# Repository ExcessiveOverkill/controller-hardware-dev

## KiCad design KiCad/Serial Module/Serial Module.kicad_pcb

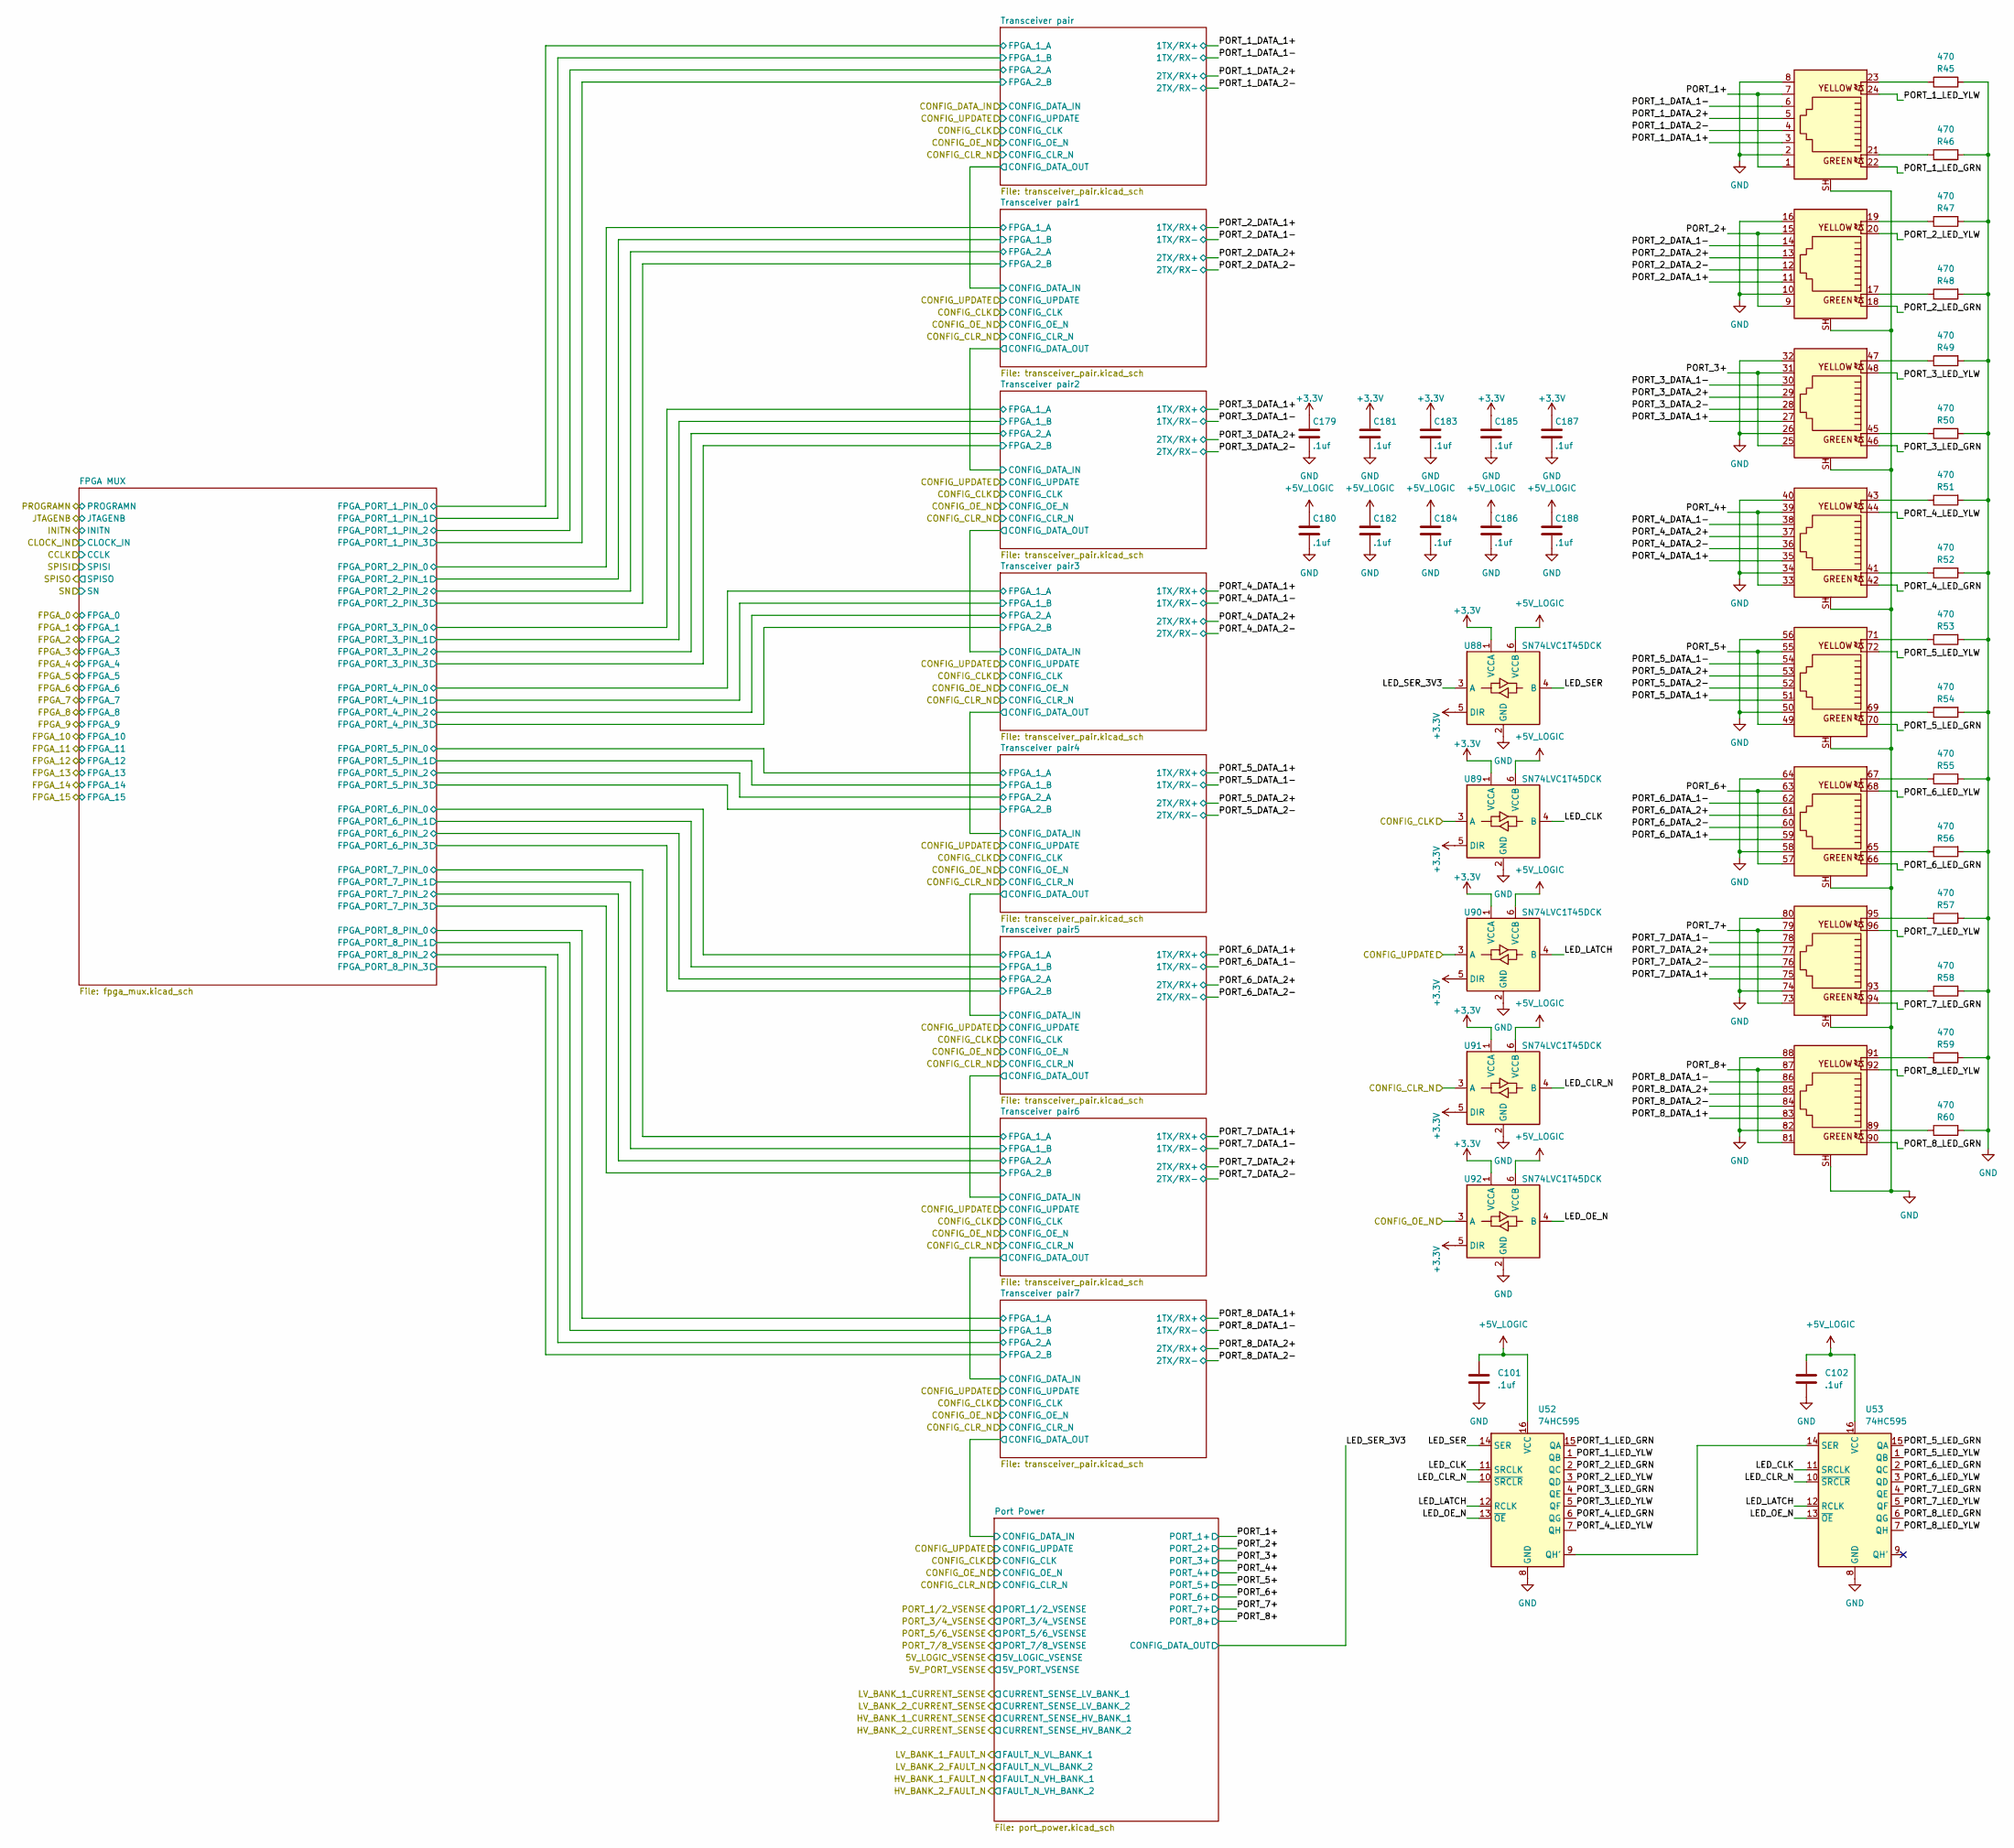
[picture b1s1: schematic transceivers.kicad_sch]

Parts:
C101, C102, C179, C180, C181, C182, C183, C184, C185, C186, C187, C188: .1uf; C_0402_1005Metric; Part number CC0402KRX7R9BB104; LCSC# C131394
J3: RJ45-TH_HC-RJ45-059D-2X4-2-04; Part number HC-RJ45-059D-2*4-2-04; LCSC# C46261621
R45, R46, R47, R48, R49, R50, R51, R52, R53, R54, R55, R56, R57, R58, R59, R60: 470; R_0402_1005Metric; Part number RC0402FR-07470RL; LCSC# C114877
U52, U53: 74HC595; DHVQFN-16-1EP_2.5x3.5mm_P0.5mm_EP1x2mm; Part number 74HC595BQ,115; LCSC# C730243
U88, U89, U90, U91, U92: SN74LVC1T45DCK; SOT-363_SC-70-6; Part number SN74LVC1T45DCKR; LCSC# C9382

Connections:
+3.3V: C179.1, C181.1, C183.1, C185.1, C187.1, U88.1 (VCCA), U88.5 (DIR), U89.1 (VCCA), U89.5 (DIR), U90.1 (VCCA), U90.5 (DIR), U91.1 (VCCA), U91.5 (DIR), U92.1 (VCCA), U92.5 (DIR); also elsewhere on the board
+5V_LOGIC: C101.1, C102.1, C180.1, C182.1, C184.1, C186.1, C188.1, U52.16 (VCC), U53.16 (VCC), U88.6 (VCCB), U89.6 (VCCB), U90.6 (VCCB), U91.6 (VCCB), U92.6 (VCCB); also elsewhere on the board
/MCU/CONFIG_CLK: U89.3 (A); also elsewhere on the board
/MCU/CONFIG_CLR_N: U91.3 (A); also elsewhere on the board
/MCU/CONFIG_OE_N: U92.3 (A); also elsewhere on the board
/MCU/CONFIG_UPDATE: U90.3 (A); also elsewhere on the board
/Transceivers/LED_CLK: U52.11 (SRCLK), U53.11 (SRCLK), U89.4 (B)
/Transceivers/LED_CLR_N: U52.10 (~SRCLR), U53.10 (~SRCLR), U91.4 (B)
/Transceivers/LED_LATCH: U52.12 (RCLK), U53.12 (RCLK), U90.4 (B)
/Transceivers/LED_OE_N: U52.13 (~OE), U53.13 (~OE), U92.4 (B)
/Transceivers/LED_SER: U52.14 (SER), U88.4 (B)
/Transceivers/LED_SER_3V3: U88.3 (A); also elsewhere on the board
/Transceivers/PORT_1+: J3.1, J3.7; also elsewhere on the board
/Transceivers/PORT_1_DATA_1+: J3.3; also elsewhere on the board
/Transceivers/PORT_1_DATA_1-: J3.6; also elsewhere on the board
/Transceivers/PORT_1_DATA_2+: J3.5; also elsewhere on the board
/Transceivers/PORT_1_DATA_2-: J3.4; also elsewhere on the board
/Transceivers/PORT_1_LED_GRN: J3.22, U52.15 (QA)
/Transceivers/PORT_1_LED_YLW: J3.24, U52.1 (QB)
/Transceivers/PORT_2+: J3.9, J3.15; also elsewhere on the board
/Transceivers/PORT_2_DATA_1+: J3.11; also elsewhere on the board
/Transceivers/PORT_2_DATA_1-: J3.14; also elsewhere on the board
/Transceivers/PORT_2_DATA_2+: J3.13; also elsewhere on the board
/Transceivers/PORT_2_DATA_2-: J3.12; also elsewhere on the board
/Transceivers/PORT_2_LED_GRN: J3.18, U52.2 (QC)
/Transceivers/PORT_2_LED_YLW: J3.20, U52.3 (QD)
/Transceivers/PORT_3+: J3.25, J3.31; also elsewhere on the board
/Transceivers/PORT_3_DATA_1+: J3.27; also elsewhere on the board
/Transceivers/PORT_3_DATA_1-: J3.30; also elsewhere on the board
/Transceivers/PORT_3_DATA_2+: J3.29; also elsewhere on the board
/Transceivers/PORT_3_DATA_2-: J3.28; also elsewhere on the board
/Transceivers/PORT_3_LED_GRN: J3.46, U52.4 (QE)
/Transceivers/PORT_3_LED_YLW: J3.48, U52.5 (QF)
/Transceivers/PORT_4+: J3.33, J3.39; also elsewhere on the board
/Transceivers/PORT_4_DATA_1+: J3.35; also elsewhere on the board
/Transceivers/PORT_4_DATA_1-: J3.38; also elsewhere on the board
/Transceivers/PORT_4_DATA_2+: J3.37; also elsewhere on the board
/Transceivers/PORT_4_DATA_2-: J3.36; also elsewhere on the board
/Transceivers/PORT_4_LED_GRN: J3.42, U52.6 (QG)
/Transceivers/PORT_4_LED_YLW: J3.44, U52.7 (QH)
/Transceivers/PORT_5+: J3.49, J3.55; also elsewhere on the board
/Transceivers/PORT_5_DATA_1+: J3.51; also elsewhere on the board
/Transceivers/PORT_5_DATA_1-: J3.54; also elsewhere on the board
/Transceivers/PORT_5_DATA_2+: J3.53; also elsewhere on the board
/Transceivers/PORT_5_DATA_2-: J3.52; also elsewhere on the board
/Transceivers/PORT_5_LED_GRN: J3.70, U53.15 (QA)
/Transceivers/PORT_5_LED_YLW: J3.72, U53.1 (QB)
/Transceivers/PORT_6+: J3.57, J3.63; also elsewhere on the board
/Transceivers/PORT_6_DATA_1+: J3.59; also elsewhere on the board
/Transceivers/PORT_6_DATA_1-: J3.62; also elsewhere on the board
/Transceivers/PORT_6_DATA_2+: J3.61; also elsewhere on the board
/Transceivers/PORT_6_DATA_2-: J3.60; also elsewhere on the board
/Transceivers/PORT_6_LED_GRN: J3.66, U53.2 (QC)
/Transceivers/PORT_6_LED_YLW: J3.68, U53.3 (QD)
/Transceivers/PORT_7+: J3.73, J3.79; also elsewhere on the board
/Transceivers/PORT_7_DATA_1+: J3.75; also elsewhere on the board
/Transceivers/PORT_7_DATA_1-: J3.78; also elsewhere on the board
/Transceivers/PORT_7_DATA_2+: J3.77; also elsewhere on the board
/Transceivers/PORT_7_DATA_2-: J3.76; also elsewhere on the board
/Transceivers/PORT_7_LED_GRN: J3.94, U53.4 (QE)
/Transceivers/PORT_7_LED_YLW: J3.96, U53.5 (QF)
/Transceivers/PORT_8+: J3.81, J3.87; also elsewhere on the board
/Transceivers/PORT_8_DATA_1+: J3.83; also elsewhere on the board
/Transceivers/PORT_8_DATA_1-: J3.86; also elsewhere on the board
/Transceivers/PORT_8_DATA_2+: J3.85; also elsewhere on the board
/Transceivers/PORT_8_DATA_2-: J3.84; also elsewhere on the board
/Transceivers/PORT_8_LED_GRN: J3.90, U53.6 (QG)
/Transceivers/PORT_8_LED_YLW: J3.92, U53.7 (QH)
GND: C101.2, C102.2, C179.2, C180.2, C181.2, C182.2, C183.2, C184.2, C185.2, C186.2, C187.2, C188.2, J3.2, J3.8, J3.10, J3.16, J3.26, J3.32, J3.34, J3.40, J3.50, J3.56, J3.58, J3.64, J3.74, J3.80, J3.82, J3.88, J3.SH, R45.2, R46.2, R47.2, R48.2, R49.2, R50.2, R51.2, R52.2, R53.2, R54.2, R55.2, R56.2, R57.2, R58.2, R59.2, R60.2, U52.8 (GND), U53.8 (GND), U88.2 (GND), U89.2 (GND), U90.2 (GND), U91.2 (GND), U92.2 (GND); also elsewhere on the board
unnamed: J3.17, R48.1
unnamed: J3.19, R47.1
unnamed: J3.21, R46.1
unnamed: J3.23, R45.1
unnamed: J3.41, R52.1
unnamed: J3.43, R51.1
unnamed: J3.45, R50.1
unnamed: J3.47, R49.1
unnamed: J3.65, R56.1
unnamed: J3.67, R55.1
unnamed: J3.69, R54.1
unnamed: J3.71, R53.1
unnamed: J3.89, R60.1
unnamed: J3.91, R59.1
unnamed: J3.93, R58.1
unnamed: J3.95, R57.1
unnamed: U52.9 (QH'), U53.14 (SER)

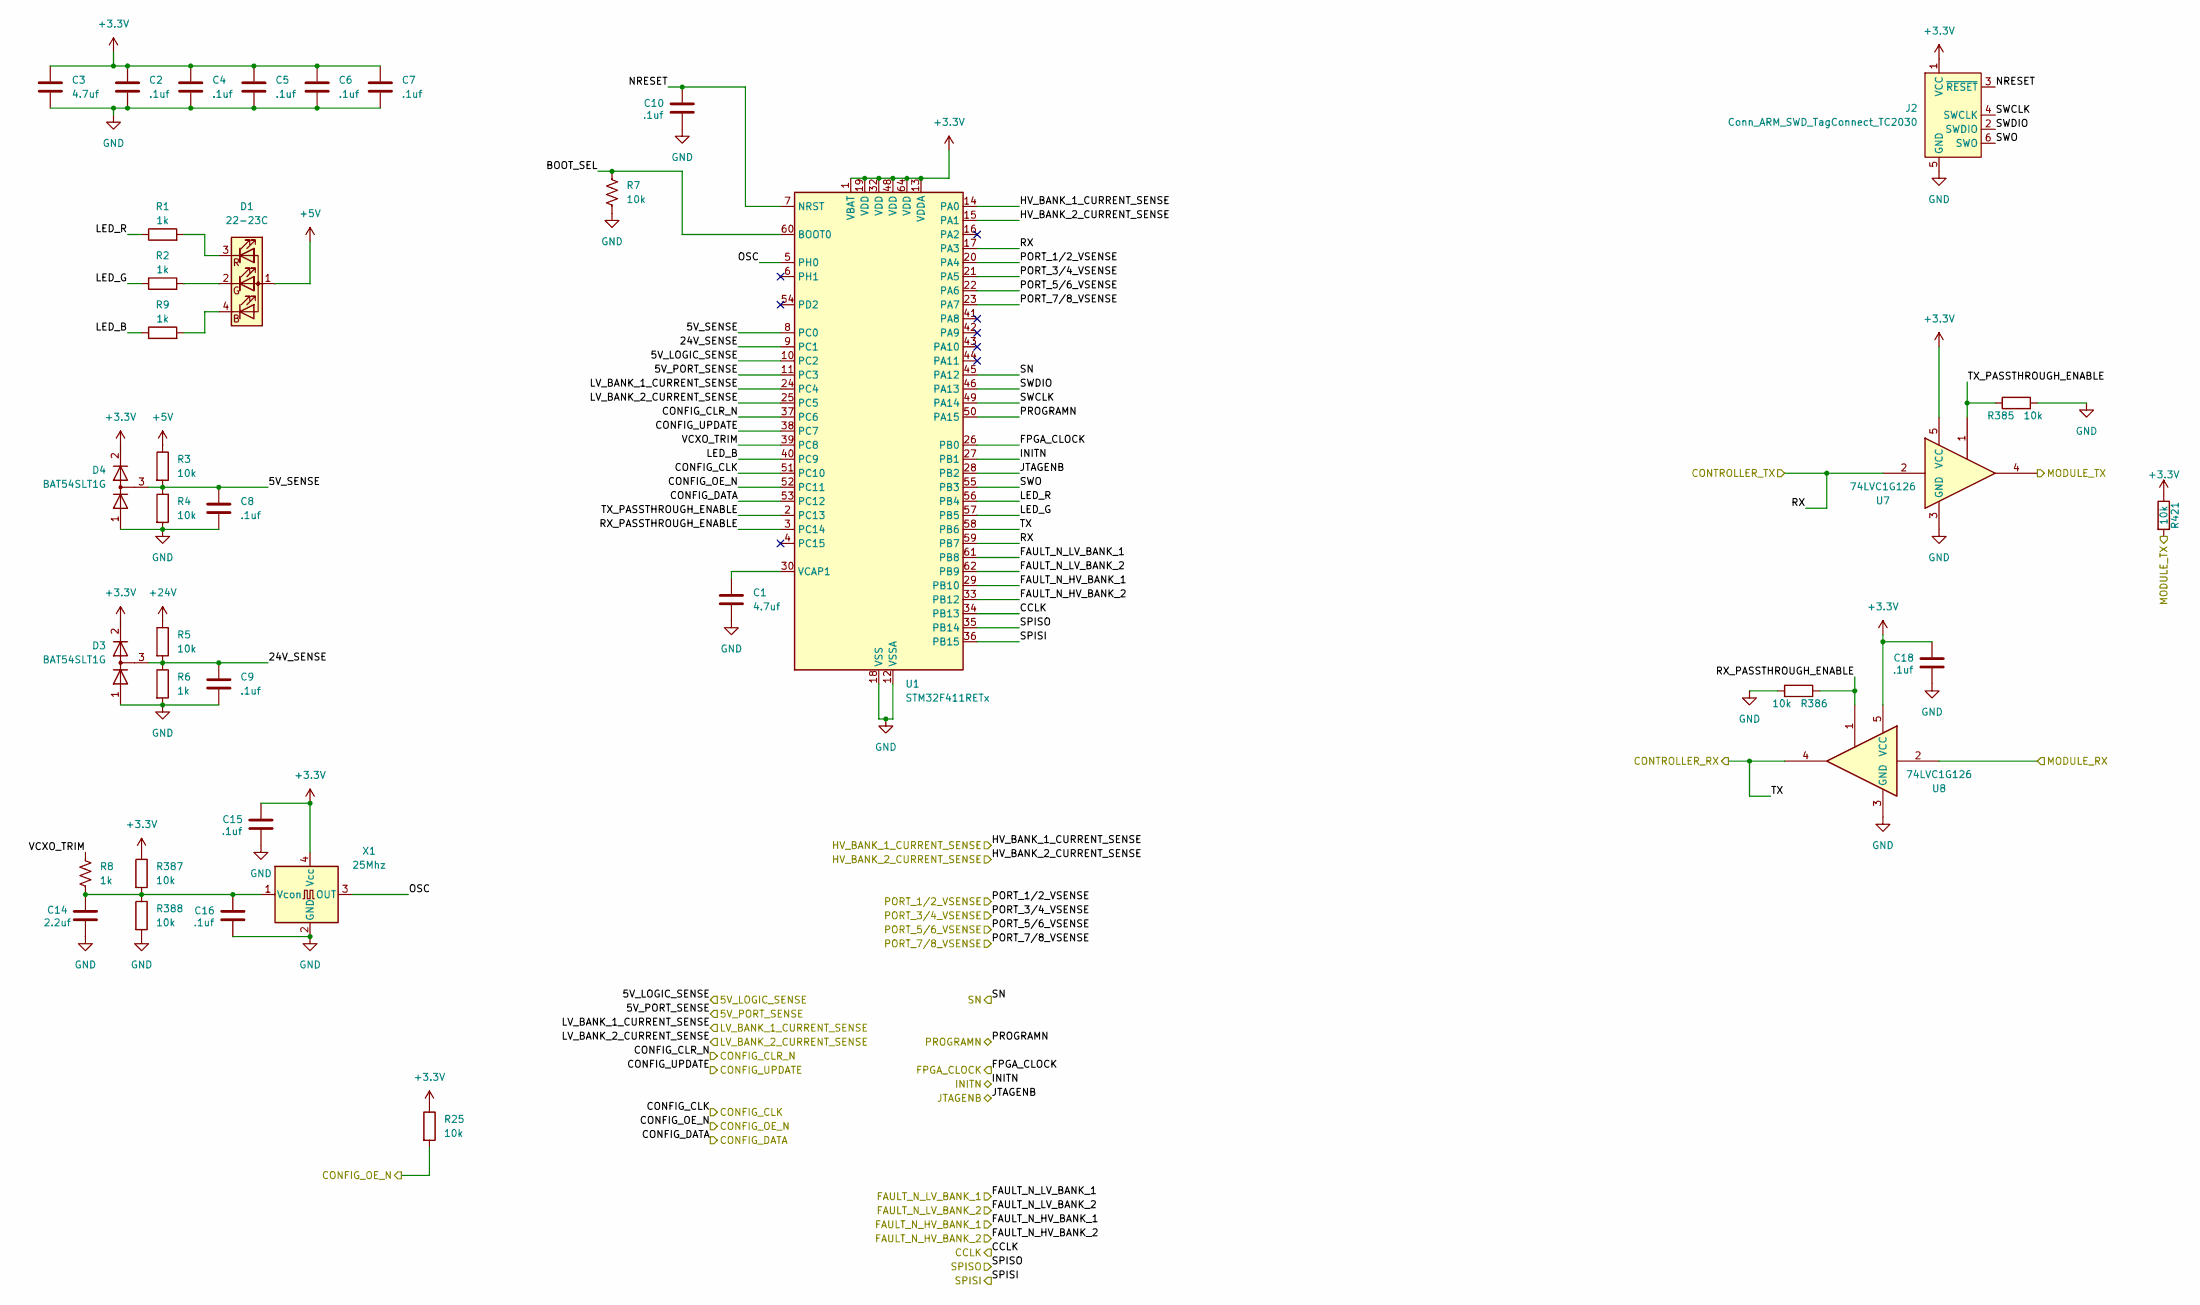
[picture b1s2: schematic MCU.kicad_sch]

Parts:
C1: 4.7uf; C_0402_1005Metric; Part number CC0402MRX5R6BB475; LCSC# C469468
C2, C4, C5, C6, C7, C8, C9, C10, C15, C16, C18: .1uf; C_0402_1005Metric; Part number CC0402KRX7R9BB104; LCSC# C131394
C3: 4.7uf; C_0603_1608Metric; Part number CC0603KRX5R7BB475; LCSC# C277476
C14: 2.2uf; C_0402_1005Metric; Part number CC0402KRX5R6BB225; LCSC# C326606
D1: 22-23C; 22-23C_EVE; Part number 22-23C/R6GHBHW-C01/2C; LCSC# C181865
D3, D4: BAT54SLT1G; SOT-23; Part number LBAT54SLT1G; LCSC# C12765
J2: Conn_ARM_SWD_TagConnect_TC2030; Tag-Connect_TC2030-IDC-FP_2x03_P1.27mm_Vertical; Part number N/A - Tag-Connect TC2030 pads only (no 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
R1, R2, R6, R8, R9: 1k; R_0402_1005Metric; Part number RC0402FR-071KL; LCSC# C106235
R3, R4, R5, R7, R25, R385, R386, R387, R388, R421: 10k; R_0402_1005Metric; Part number RC0402FR-0710KL; LCSC# C60490
U1: STM32F411RETx; LQFP-64_10x10mm_P0.5mm; Part number STM32F411RET6; LCSC# C94355
U7, U8: 74LVC1G126; SOT-353_SC-70-5; Part number 74LVC1G126CT05ARCQ; LCSC# C48391411
X1: 25Mhz; Oscillator_SMD_Abracon_ASE-4Pin_3.2x2.5mm; Part number SX3V25.000B20100F30TNN; LCSC# C5179998

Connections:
+3.3V: C2.1, C3.1, C4.1, C5.1, C6.1, C7.1, C15.2, C18.2, D3.2 (K), D4.2 (K), J2.1 (VCC), R25.1, R387.1, R421.1, U1.1 (VBAT), U1.13 (VDDA), U1.19 (VDD), U1.32 (VDD), U1.48 (VDD), U1.64 (VDD), U7.5 (VCC), U8.5 (VCC), X1.4 (Vcc); also elsewhere on the board
+5V: D1.1 (A), R3.1; also elsewhere on the board
+24V: R5.1; also elsewhere on the board
/FPGA Connector/MODULE_RX: U8.2; also elsewhere on the board
/FPGA Connector/MODULE_TX: R421.2, U7.4; also elsewhere on the board
/MCU/5V_LOGIC_SENSE: U1.10 (PC2); also elsewhere on the board
/MCU/5V_PORT_SENSE: U1.11 (PC3); also elsewhere on the board
/MCU/5V_SENSE: C8.1, D4.3 (common), R3.2, R4.1, U1.8 (PC0)
/MCU/24V_SENSE: C9.1, D3.3 (common), R5.2, R6.1, U1.9 (PC1)
/MCU/BOOT_SEL: R7.2, U1.60 (BOOT0)
/MCU/CCLK: U1.34 (PB13); also elsewhere on the board
/MCU/CONFIG_CLK: U1.51 (PC10); also elsewhere on the board
/MCU/CONFIG_CLR_N: U1.37 (PC6); also elsewhere on the board
/MCU/CONFIG_DATA: U1.53 (PC12); also elsewhere on the board
/MCU/CONFIG_OE_N: R25.2, U1.52 (PC11); also elsewhere on the board
/MCU/CONFIG_UPDATE: U1.38 (PC7); also elsewhere on the board
/MCU/FAULT_N_HV_BANK_1: U1.29 (PB10); also elsewhere on the board
/MCU/FAULT_N_HV_BANK_2: U1.33 (PB12); also elsewhere on the board
/MCU/FAULT_N_LV_BANK_1: U1.61 (PB8); also elsewhere on the board
/MCU/FAULT_N_LV_BANK_2: U1.62 (PB9); also elsewhere on the board
/MCU/FPGA_CLOCK: U1.26 (PB0); also elsewhere on the board
/MCU/HV_BANK_1_CURRENT_SENSE: U1.14 (PA0); also elsewhere on the board
/MCU/HV_BANK_2_CURRENT_SENSE: U1.15 (PA1); also elsewhere on the board
/MCU/INITN: U1.27 (PB1); also elsewhere on the board
/MCU/JTAGENB: U1.28 (PB2); also elsewhere on the board
/MCU/LED_B: R9.1, U1.40 (PC9)
/MCU/LED_G: R2.1, U1.57 (PB5)
/MCU/LED_R: R1.1, U1.56 (PB4)
/MCU/LV_BANK_1_CURRENT_SENSE: U1.24 (PC4); also elsewhere on the board
/MCU/LV_BANK_2_CURRENT_SENSE: U1.25 (PC5); also elsewhere on the board
/MCU/NRESET: C10.2, J2.3 (~RESET), U1.7 (NRST)
/MCU/OSC: U1.5 (PH0), X1.3 (OUT)
/MCU/PORT_1/2_VSENSE: U1.20 (PA4); also elsewhere on the board
/MCU/PORT_3/4_VSENSE: U1.21 (PA5); also elsewhere on the board
/MCU/PORT_5/6_VSENSE: U1.22 (PA6); also elsewhere on the board
/MCU/PORT_7/8_VSENSE: U1.23 (PA7); also elsewhere on the board
/MCU/PROGRAMN: U1.50 (PA15); also elsewhere on the board
/MCU/RX: U1.17 (PA3), U1.59 (PB7), U7.2; also elsewhere on the board
/MCU/RX_PASSTHROUGH_ENABLE: R386.1, U1.3 (PC14), U8.1
/MCU/SN: U1.45 (PA12); also elsewhere on the board
/MCU/SPISI: U1.36 (PB15); also elsewhere on the board
/MCU/SPISO: U1.35 (PB14); also elsewhere on the board
/MCU/SWCLK: J2.4 (SWCLK), U1.49 (PA14)
/MCU/SWDIO: J2.2 (SWDIO), U1.46 (PA13)
/MCU/SWO: J2.6 (SWO), U1.55 (PB3)
/MCU/TX: U1.58 (PB6), U8.4; also elsewhere on the board
/MCU/TX_PASSTHROUGH_ENABLE: R385.1, U1.2 (PC13), U7.1
/MCU/VCXO_TRIM: R8.1, U1.39 (PC8)
GND: C1.2, C2.2, C3.2, C4.2, C5.2, C6.2, C7.2, C8.2, C9.2, C10.1, C14.1, C15.1, C16.1, C18.1, D3.1 (A), D4.1 (A), J2.5 (GND), R4.2, R6.2, R7.1, R385.2, R386.2, R388.2, U1.12 (VSSA), U1.18 (VSS), U1.31 (VSS), U1.47 (VSS), U1.63 (VSS), U7.3 (GND), U8.3 (GND), X1.2 (GND); also elsewhere on the board
unnamed: D1.4 (BK), R9.2
unnamed: D1.2 (GK), R2.2
unnamed: D1.3 (RK), R1.2
unnamed: C1.1, U1.30 (VCAP1)
unnamed: C14.2, C16.2, R8.2, R387.2, R388.1, X1.1 (Vcon)

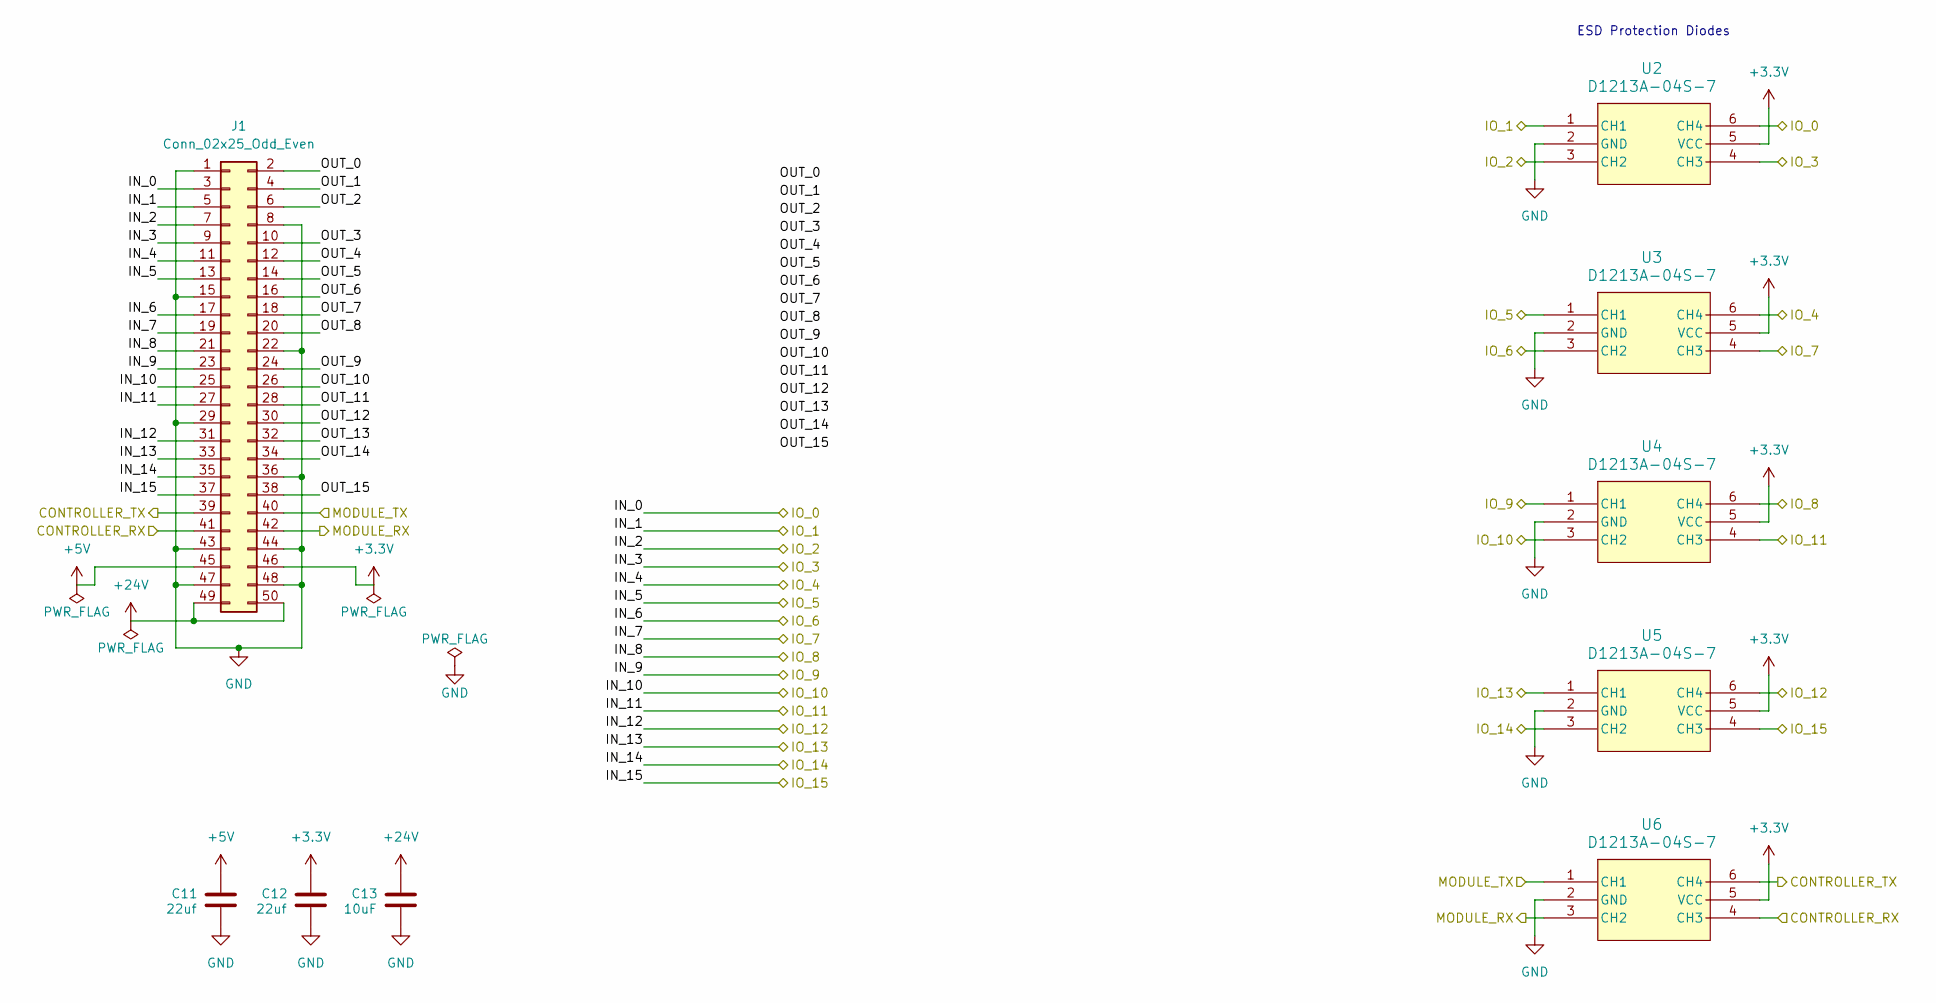
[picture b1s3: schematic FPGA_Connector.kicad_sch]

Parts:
C11, C12: 22uf; C_0805_2012Metric; Part number CC0805MKX5R8BB226; LCSC# C784585
C13: 10uF; C_1210_3225Metric; Part number CC1210KKX7R9BB106; LCSC# C596319
J1: Conn_02x25_Odd_Even; 16x_modular_card; Part number X4621WR-2x25I-C40D28; LCSC# C2883281
U2, U3, U4, U5, U6: D1213A-04S-7; SOT-363_SC-70-6; Part number D1213A-04S-7-ES; LCSC# C41409235

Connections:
+3.3V: C12.2, J1.46, U2.5 (VCC), U3.5 (VCC), U4.5 (VCC), U5.5 (VCC), U6.5 (VCC); also elsewhere on the board
+5V: C11.2, J1.45; also elsewhere on the board
+24V: C13.2, J1.49, J1.50; also elsewhere on the board
/FPGA Connector/IN_0: J1.3, U2.6 (CH4); also elsewhere on the board
/FPGA Connector/IN_1: J1.5, U2.1 (CH1); also elsewhere on the board
/FPGA Connector/IN_2: J1.7, U2.3 (CH2); also elsewhere on the board
/FPGA Connector/IN_3: J1.9, U2.4 (CH3); also elsewhere on the board
/FPGA Connector/IN_4: J1.11, U3.6 (CH4); also elsewhere on the board
/FPGA Connector/IN_5: J1.13, U3.1 (CH1); also elsewhere on the board
/FPGA Connector/IN_6: J1.17, U3.3 (CH2); also elsewhere on the board
/FPGA Connector/IN_7: J1.19, U3.4 (CH3); also elsewhere on the board
/FPGA Connector/IN_8: J1.21, U4.6 (CH4); also elsewhere on the board
/FPGA Connector/IN_9: J1.23, U4.1 (CH1); also elsewhere on the board
/FPGA Connector/IN_10: J1.25, U4.3 (CH2); also elsewhere on the board
/FPGA Connector/IN_11: J1.27, U4.4 (CH3); also elsewhere on the board
/FPGA Connector/IN_12: J1.31, U5.6 (CH4); also elsewhere on the board
/FPGA Connector/IN_13: J1.33, U5.1 (CH1); also elsewhere on the board
/FPGA Connector/IN_14: J1.35, U5.3 (CH2); also elsewhere on the board
/FPGA Connector/IN_15: J1.37, U5.4 (CH3); also elsewhere on the board
/FPGA Connector/MODULE_RX: J1.42, U6.3 (CH2); also elsewhere on the board
/FPGA Connector/MODULE_TX: J1.40, U6.1 (CH1); also elsewhere on the board
/FPGA Connector/OUT_0: J1.2
/FPGA Connector/OUT_1: J1.4
/FPGA Connector/OUT_2: J1.6
/FPGA Connector/OUT_3: J1.10
/FPGA Connector/OUT_4: J1.12
/FPGA Connector/OUT_5: J1.14
/FPGA Connector/OUT_6: J1.16
/FPGA Connector/OUT_7: J1.18
/FPGA Connector/OUT_8: J1.20
/FPGA Connector/OUT_9: J1.24
/FPGA Connector/OUT_10: J1.26
/FPGA Connector/OUT_11: J1.28
/FPGA Connector/OUT_12: J1.30
/FPGA Connector/OUT_13: J1.32
/FPGA Connector/OUT_14: J1.34
/FPGA Connector/OUT_15: J1.38
/MCU/RX: J1.39, U6.6 (CH4); also elsewhere on the board
/MCU/TX: J1.41, U6.4 (CH3); also elsewhere on the board
GND: C11.1, C12.1, C13.1, J1.1, J1.8, J1.15, J1.22, J1.29, J1.36, J1.43, J1.44, J1.47, J1.48, U2.2 (GND), U3.2 (GND), U4.2 (GND), U5.2 (GND), U6.2 (GND); also elsewhere on the board

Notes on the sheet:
ESD Protection Diodes
